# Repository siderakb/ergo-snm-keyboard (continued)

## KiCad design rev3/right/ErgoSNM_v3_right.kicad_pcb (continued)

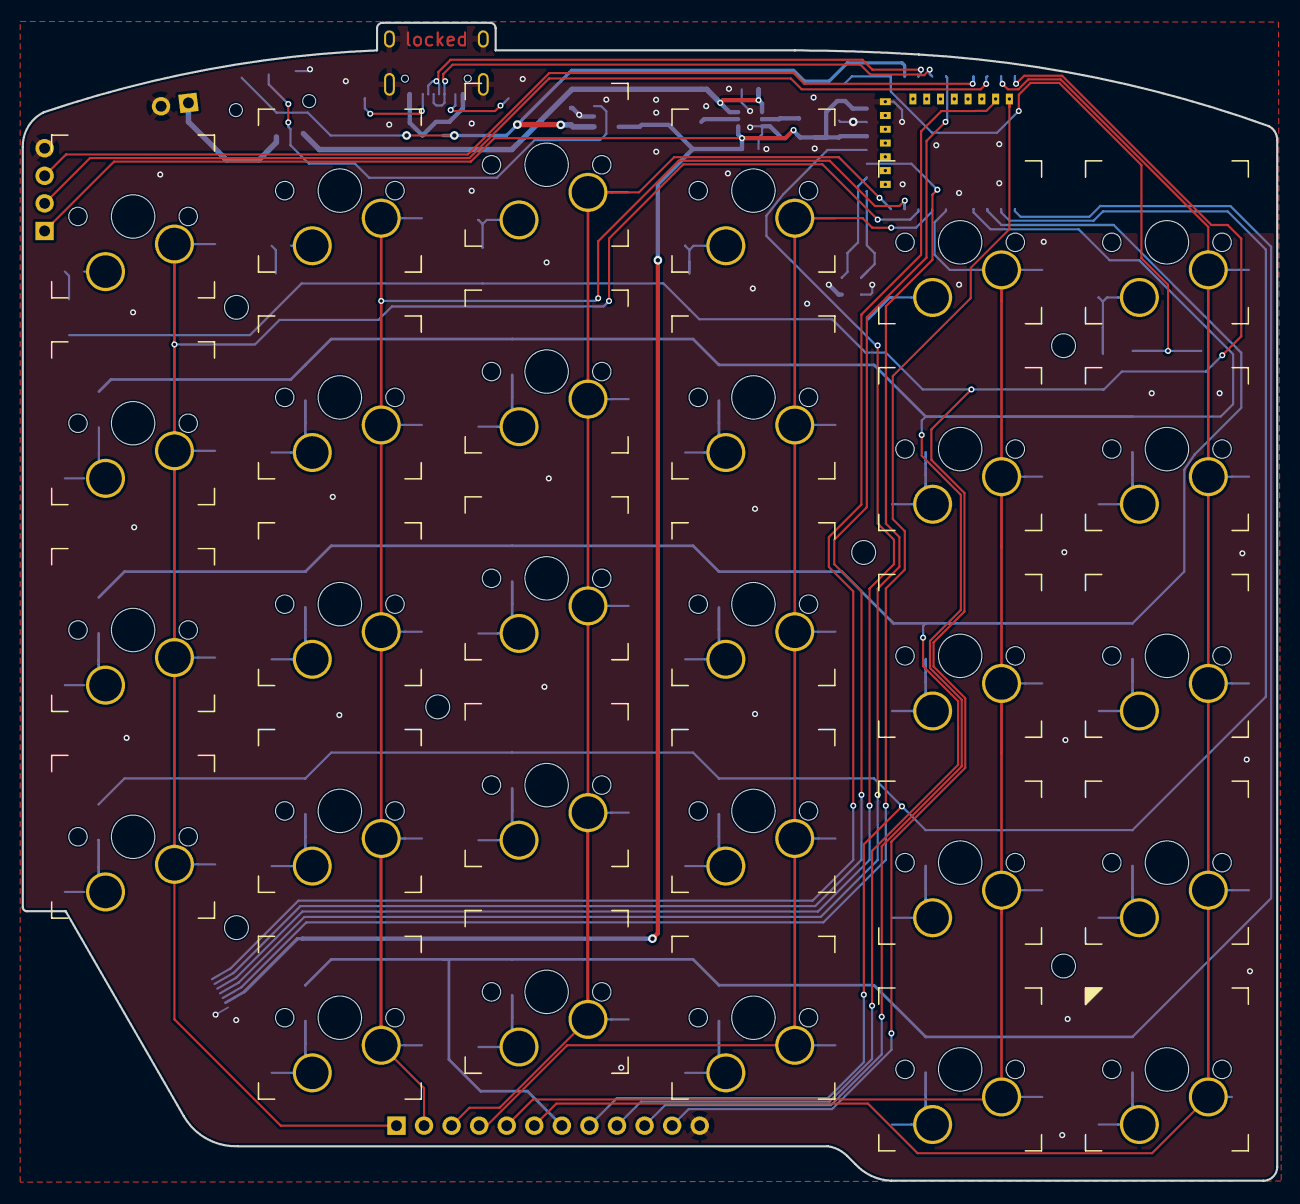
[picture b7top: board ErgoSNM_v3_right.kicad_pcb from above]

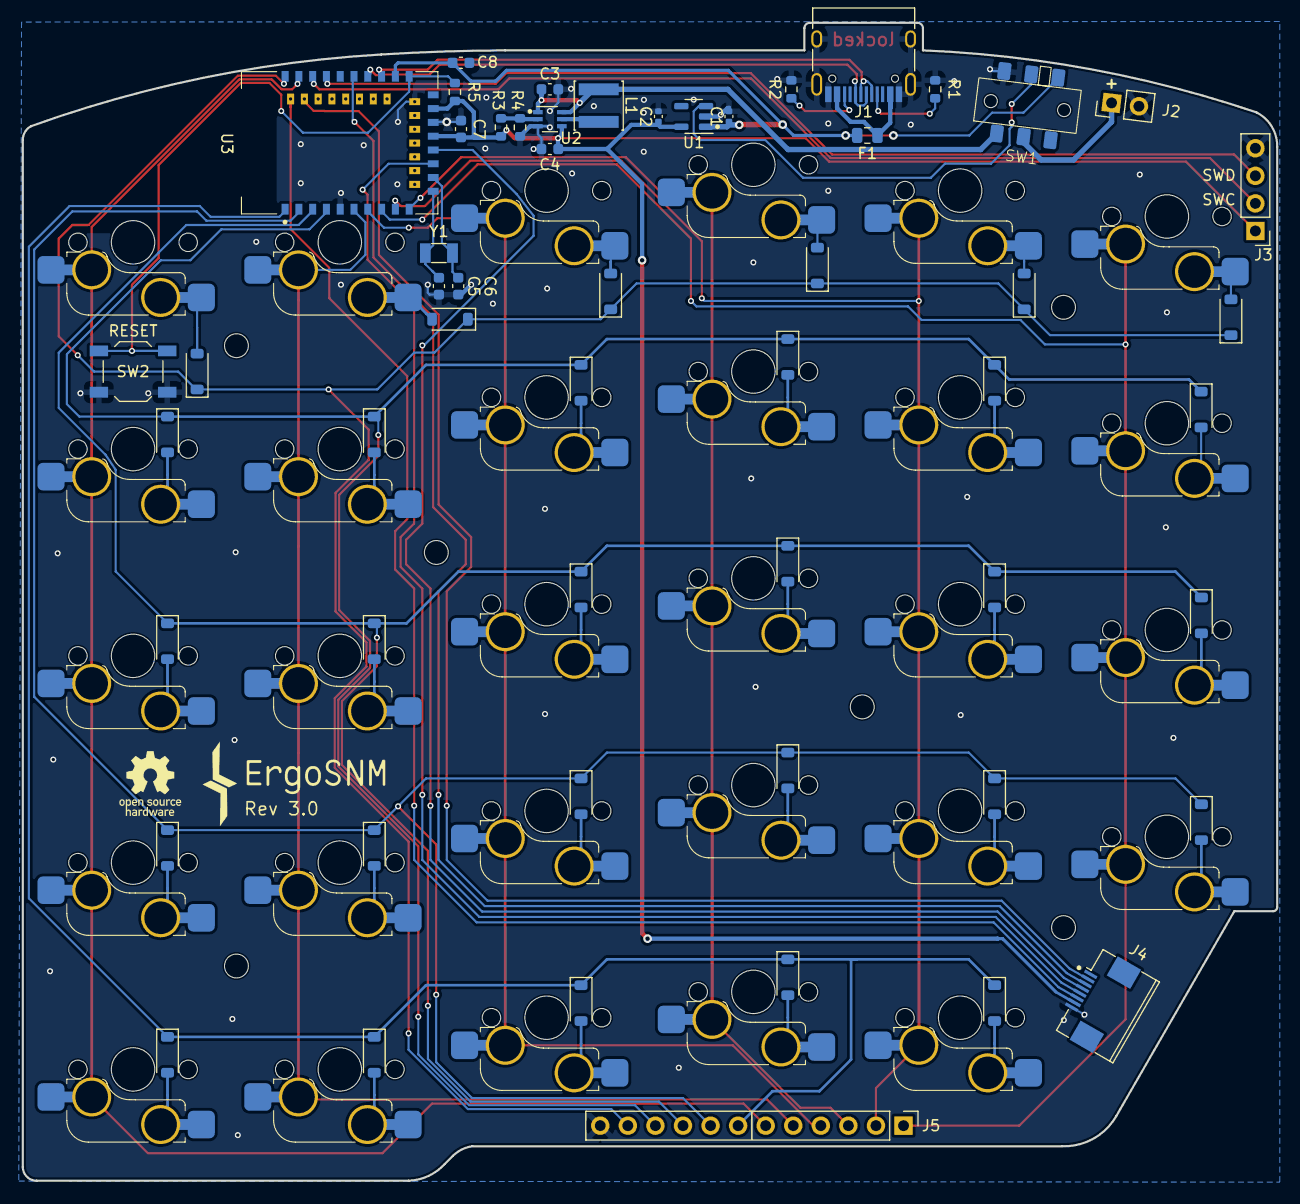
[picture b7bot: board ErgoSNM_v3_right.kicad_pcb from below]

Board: 2 copper layers, 115.6 x 106.7 mm, 90 parts (55 on the bottom side), 63 nets.

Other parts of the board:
C5, C6: 12pF; C_0603_1608Metric
C7, C8: 10uF; C_0603_1608Metric
R5: 10k; R_0603_1608Metric
SW2: RESET; SW_SPST_TL3342
U3: E73-2G4M08S1C; E73-2G4M08S1C-52840
Y1: 32.768kHz; Crystal_SMD_3215-2Pin_3.2x1.5mm

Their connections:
+5V: C8.1, U3.27 (VBUS); also elsewhere on the board
COL_0: U3.41 (P0.09/NFC1); also elsewhere on the board
COL_1: U3.6 (P1.13); also elsewhere on the board
COL_2: U3.7 (P0.02); also elsewhere on the board
COL_3: U3.10 (P0.30); also elsewhere on the board
COL_4: U3.9 (P0.31); also elsewhere on the board
COL_5: U3.8 (P0.29); also elsewhere on the board
GND: C5.2, C6.1, C7.2, C8.2, SW2.1, U3.5 (GND), U3.21 (GND), U3.24 (GND); also elsewhere on the board
unnamed: C5.1, U3.11 (P0.00/XL1), Y1.2
unnamed: C6.2, U3.13 (P0.01/XL2), Y1.1
PMW3360_Motion: U3.40 (P1.04); also elsewhere on the board
PMW3360_SPI_CS: U3.42 (P1.06); also elsewhere on the board
PMW3360_SPI_MISO: U3.15 (P0.05); also elsewhere on the board
PMW3360_SPI_MOSI: U3.17 (P1.09); also elsewhere on the board
PMW3360_SPI_SCLK: U3.33 (P0.13); also elsewhere on the board
ROW_0: U3.43 (P0.10/NFC2); also elsewhere on the board
ROW_1: U3.4 (P0.28); also elsewhere on the board
ROW_2: U3.3 (P0.03); also elsewhere on the board
ROW_3: U3.2 (P1.10); also elsewhere on the board
ROW_4: U3.1 (P1.11); also elsewhere on the board
SWC: U3.39 (SWCLK); also elsewhere on the board
SWD: U3.37 (SWDIO); also elsewhere on the board
USB_D+: U3.31 (D+); also elsewhere on the board
USB_D-: U3.29 (D-); also elsewhere on the board
VDD: C7.1, R5.1, U3.19 (VDD), U3.23 (VDDH); also elsewhere on the board
~RESET: R5.2, SW2.2, U3.26 (P0.18/RST)

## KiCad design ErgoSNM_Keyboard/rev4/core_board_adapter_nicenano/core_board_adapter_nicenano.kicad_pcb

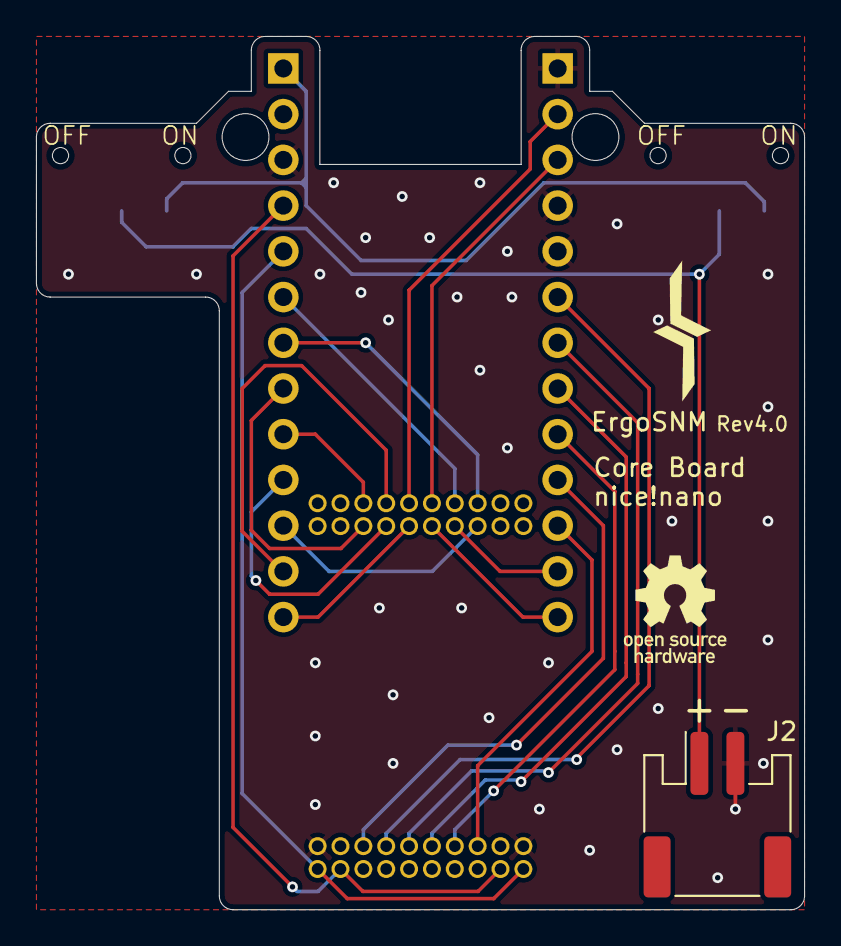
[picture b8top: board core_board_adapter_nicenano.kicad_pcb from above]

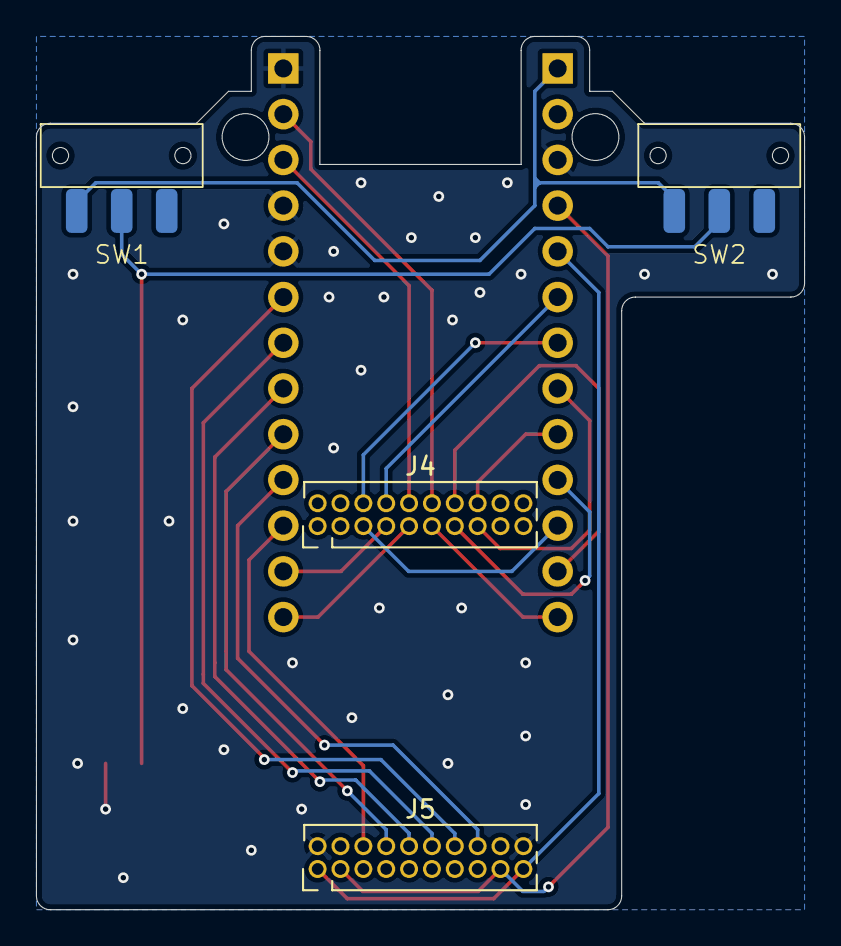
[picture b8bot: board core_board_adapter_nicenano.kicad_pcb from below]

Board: 2 copper layers, 42.7 x 48.5 mm, 9 parts (6 on the bottom side), 23 nets.

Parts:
H1, H2: MountingHole; MountingHole_2.7mm_M2.5_ISO7380
J1, J3: Conn_01x13; PinHeader_1x13_P2.54mm_Vertical
J2: Conn_Batt; JST_PH_S2B-PH-SM4-TB_1x02-1MP_P2.00mm_Horizontal
J4, J5: Conn_02x10_Odd_Even; PinHeader_2x10_P1.27mm_Vertical
SW1, SW2: SW_SPDT; 9_3.5_3.5_switch

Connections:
+3.3V: J3.5, J5.1, J5.19
+BATT: J3.1, SW1.1 (A), SW2.1 (A)
GND: J1.1, J1.4, J1.5, J2.2, J3.3, J5.2, J5.20
unnamed: J2.1, SW1.2 (B), SW2.2 (B)
P0.02: J3.8, J4.15
P0.06: J1.2, J4.12
P0.08: J1.3, J4.10
P0.09: J3.13, J4.11
P0.10: J3.12, J4.14
P0.11: J1.11, J5.6
P0.17: J1.6, J5.14
P0.20: J1.7, J5.12
P0.22: J1.8, J5.10
P0.24: J1.9, J5.8
P0.29: J3.7, J4.6
P0.31: J3.6, J4.8
P1.00: J1.10, J5.16
P1.04: J1.12, J4.7
P1.06: J1.13, J4.9
P1.11: J3.11, J4.5
P1.13: J3.10, J4.13
P1.15: J3.9, J4.16
RESET: J3.4, J5.3, J5.17

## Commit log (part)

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2022-02-27 Add README.md
2022-02-27 Add submodule
2022-02-27 Add .gitignore
2022-02-27 Add KiCad Sch and PCB Files
2022-02-27 Add Pro Micro Symbol
2022-02-27 Add footprint for Pro Micro
2022-02-28 Update Sch file
2022-03-21 Update PCB
2022-03-26 Add ErgoSNM prototype right side
2022-10-28 Update key-switches footprint library submodule
2022-10-28 Change path
2022-10-28 Create new KiCad project
2022-10-28 Update sch
2022-10-30 Add mark
2022-11-01 Add EC56_rotary encoder KiCad project
2022-11-02 Update footprint
2022-11-02 Move 1N4148s away from key switches
2022-11-03 Create LICENSE
2022-11-03 Update submodule for key switch footprint
2022-11-16 Move KiCad project
2022-11-16 Rename and fix the typo
2022-11-16 Move an rename prototype KiCad project
2022-11-20 Create Rev2
2022-11-20 Update submodule
2022-11-21 Update rev2
2022-11-25 Add logo
2022-12-11 Update `Rev 1.1`
2022-12-19 Update BOM, net, placement, etc.
2022-12-20 Update RT9013 LDO placement and add logo
2022-12-20 Copy left to right
2023-01-20 Add thumb cluster PCB
2023-01-20 Update left
2023-01-20 Update right hand schematic
2023-01-31 Update right PCB
2023-01-31 Update silk and logo
2023-01-31 Add vial 'Enter' key mark
2023-02-01 Update logo
2023-02-11 Add Rev2.0 plate KiCad files
2023-02-26 Replace JST GH 1.25 connector with 0.5mm FPC
2023-02-28 Update FPC connection and add additional LED LD2
2023-02-28 Add additional LED and upadrte LED position
2023-03-07 Add mount holes to plate
2023-03-27 Update plate
2023-03-27 Add plate panel
2023-04-29 Add keyboard-layout-editor JSON file
2023-04-29 Add footprint and symbol library path table
2023-06-25 Update URL
    replace "ziteh" with "siderakb"
2023-07-04 Update key-switches.pretty git submodule URL
2023-07-17 Update footprint library submodule
2023-10-21 Add KiCad project for ErgoSNM Rev3
2023-11-14 Add LDO for USB
2023-11-14 Add key-matrix test pointes (2.54mm pin header)
2023-11-14 Add left hand
2023-11-14 Add receiver KiCad project
2023-11-14 Update submodule
    Update submodule
    Update switch footprint
2023-11-14 Change license to CERN-OHL-P v2
2023-11-27 Fix link in readme
    The Docs link in the readme leads to a non-existent page. Should probably go to the intro page.
2024-05-28 Update issue templates
2025-02-20 chore: create core board KiCad project
2025-02-20 feat: add SNM_Core_board symbol and footprint
2025-03-25 feat: add core board and battery board defined
2025-03-25 docs: update readme
2025-04-17 feat: add v4 battery & core board
2025-04-17 chore: add .gitattributes
2025-06-28 chore: update key-switches
2025-06-28 feat: create adapter nice nano
2025-06-28 feat: add ErgoSNM v4 main board, schematic
2025-07-04 feat: add v4 mdbt50q board
2025-07-04 refactor: rename KiCad project
2025-07-05 feat: update main board layout
2025-07-09 feat: routed E73 core board
2025-07-15 feat: update USB ESD
2025-07-20 feat: change Buck-Boost DC/DC IC from TPS63020 to TPS63900
2025-07-20 feat: add 4x M2.5 mounting hole
2025-07-23 feat: add top case FreeCAD file
2025-07-24 feat: update main board layout for 1.27mm pin header
2025-07-29 feat: change pin header position
2025-07-29 feat: add thumb cluster
2025-09-11 feat: update the connectors of the main board and core board
2025-09-20 feat: update nice!nano core board
2025-09-21 feat: update E73 core board
2025-09-21 chore: add gitattributes
2025-09-21 chore: update gitignore
2025-09-21 feat: update BOM
2025-09-21 feat: add stats and change LED
2025-10-06 fix: add B5819 for battery reverse protection
2025-11-01 feat: add 3D models (USB-C, TRRS, Switch)
2025-11-01 chore: update submodule
2025-11-01 chore: remove the local library and replace it with a submodule
2025-11-01 chore: remove unused legacy projects
2025-11-01 chore: adjust the folder structure
2025-11-01 fix: update footprint and symbol lib path
2025-11-01 chore: update .gitignore
2025-11-01 feat: add FreeCAD left case 3D model
2025-11-02 feat: reduce Y length
2025-11-03 feat: add right case 3D model
2025-11-03 fix: update legs length
2025-11-08 fix: update top case rid
2026-02-25 feat: update double switch layout
2026-03-01 chore: update switch lib submodule
2026-03-02 feat: create main board kicad project
2026-03-02 chore: update key switches submodule
2026-03-04 feat: add basic parts
2026-03-29 feat: update placement
2026-03-29 feat: add core board e73
2026-03-29 feat: basic routed
2026-03-30 feat: core board e73 basic routed
2026-03-30 feat: add DCDC zone
2026-03-30 feat: update silkscreen
2026-04-03 feat: update title block
